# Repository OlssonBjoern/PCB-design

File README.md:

# PCB-design
Different PCB-designs to practice design in KiCad

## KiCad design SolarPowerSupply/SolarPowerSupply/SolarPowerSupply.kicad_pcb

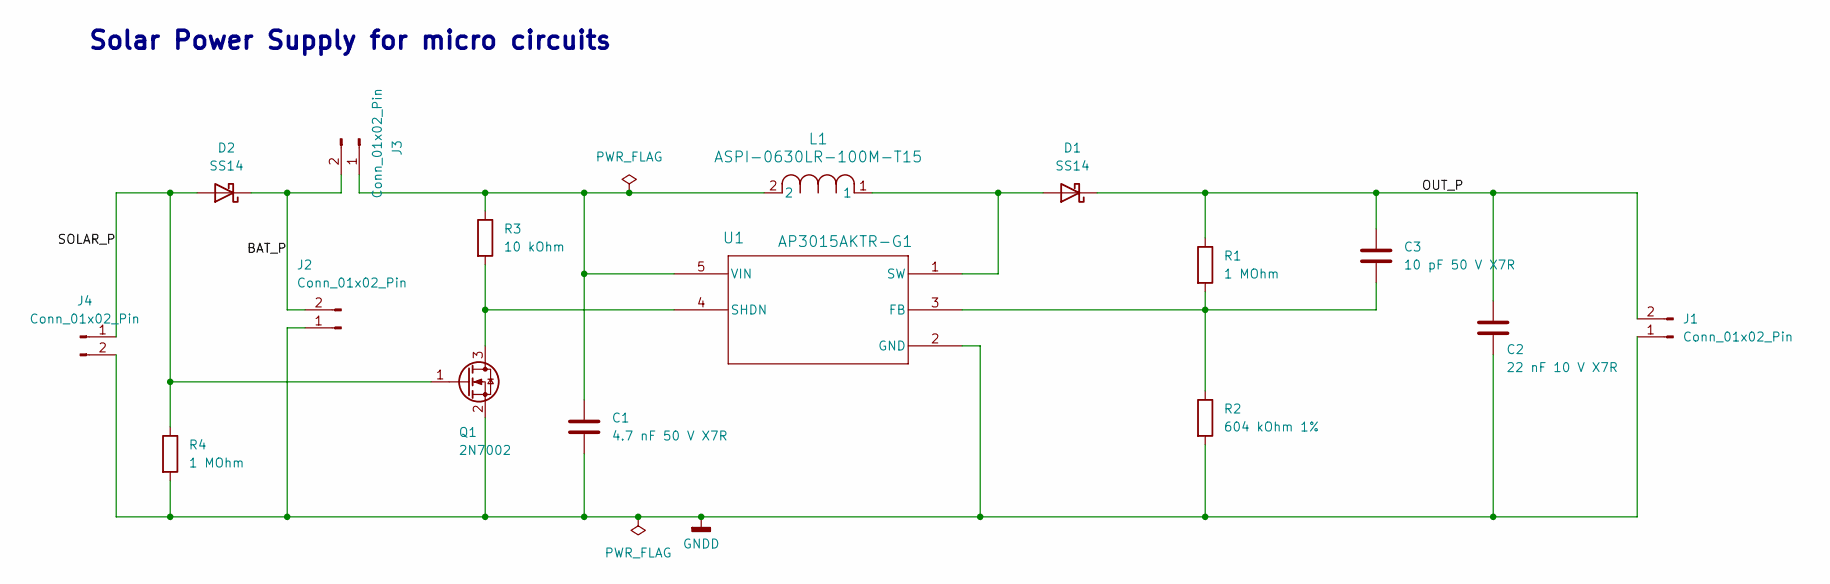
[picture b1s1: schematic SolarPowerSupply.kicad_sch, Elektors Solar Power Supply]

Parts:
C1: 4.7 nF 50 V X7R; C_0805_2012Metric
C2: 22 nF 10 V X7R; C_1206_3216Metric
C3: 10 pF 50 V X7R; C_0805_2012Metric
D1, D2: SS14; D_SMA
J1, J2: Conn_01x02_Pin; PinHeader_1x02_P2.54mm_Horizontal
J3: Conn_01x02_Pin; SW_DIP_SPSTx01_Slide_9.78x4.72mm_W7.62mm_P2.54mm
J4: Conn_01x02_Pin; PinHeader_1x02_P2.00mm_Horizontal
L1: ASPI-0630LR-100M-T15; IND_ASPI-0630LR_ABR
Q1: 2N7002; SOT-23
R1, R4: 1 MOhm; R_0805_2012Metric
R2: 604 kOhm 1%; R_0805_2012Metric
R3: 10 kOhm; R_0805_2012Metric
U1: AP3015AKTR-G1; SOT23-5_1P55X2P9_DIO

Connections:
/<NO NET>: C2.1, C3.1, D1.1 (K), J1.2, R1.1
/BAT_P: D2.1 (K), J2.2, J3.2
/SOLAR_P: D2.2 (A), J4.1, Q1.1 (G), R4.1
GNDD: C1.2, C2.2, J1.1, J2.1, J4.2, Q1.2 (S), R2.2, R4.2, U1.2 (GND)
unnamed: D1.2 (A), L1.1, U1.1 (SW)
unnamed: C1.1, J3.1, L1.2, R3.1, U1.5 (VIN)
unnamed: Q1.3 (D), R3.2, U1.4 (SHDN)
unnamed: C3.2, R1.2, R2.1, U1.3 (FB)

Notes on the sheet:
Solar Power Supply for micro circuits

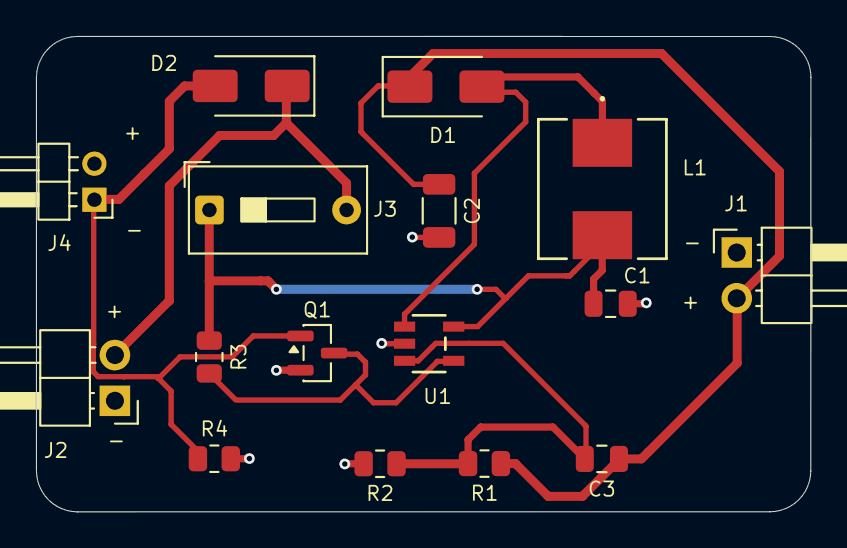
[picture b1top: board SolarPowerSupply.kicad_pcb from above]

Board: 2 copper layers, 43.0 x 26.4 mm, 16 parts (0 on the bottom side), 8 nets.

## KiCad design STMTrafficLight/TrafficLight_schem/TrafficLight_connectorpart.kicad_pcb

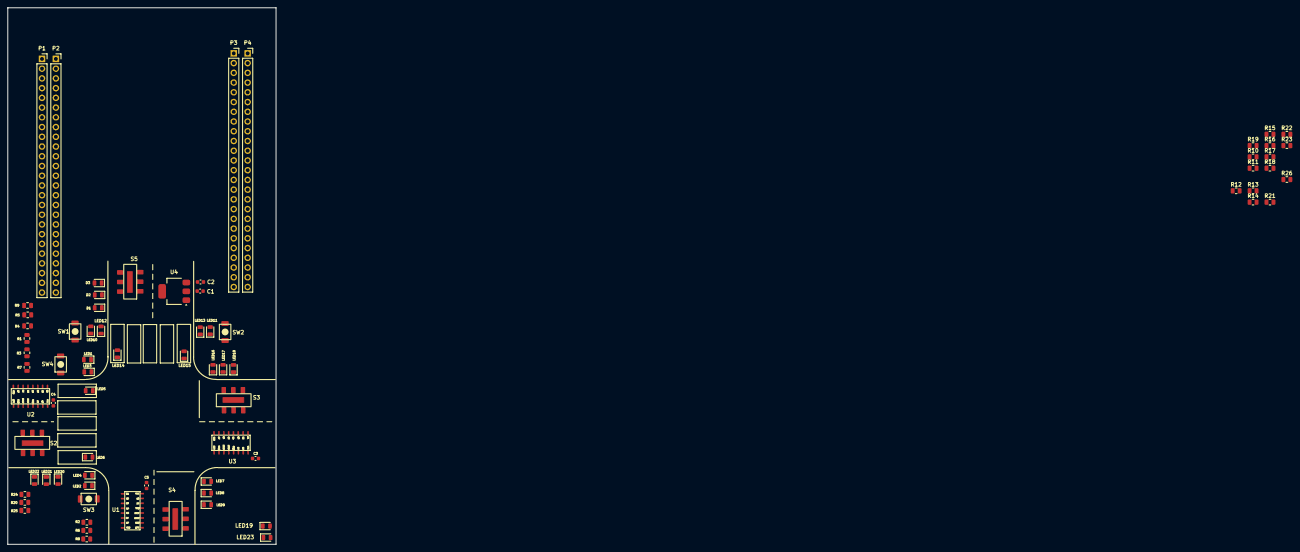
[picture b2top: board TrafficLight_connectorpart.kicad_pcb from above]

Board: 2 copper layers, 70.0 x 140.0 mm, 73 parts (0 on the bottom side), 56 nets, no tracks yet.

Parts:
C1, C2: 10uF; C_0603_1608Metric
C3, C4, C5: 100 nF; C_0603_1608Metric
D1: Red; LED_0805_2012Metric
D2: yellow; LED_0805_2012Metric
D3: green; LED_0805_2012Metric
LED1, LED2, LED7, LED10, LED11, LED16, LED20, LED23: Red; LED_0805_2012Metric
LED3, LED4, LED9, LED12, LED13, LED18, LED22: green; LED_0805_2012Metric
LED5, LED6, LED8, LED14, LED15, LED17, LED21: yellow; LED_0805_2012Metric
LED19: Green; LED_0805_2012Metric
P1, P2, P3, P4: Conn_01x25; PinSocket_1x25_P2.54mm_Vertical
R1, R2, R4, R5, R7, R8, R10, R11, R13, R14, R15, R16, R21, R22, R24, R25: 330; R_0805_2012Metric
R3, R6, R9, R12, R17, R18, R19, R20: 220; R_0805_2012Metric
R23, R26: 1k; R_0805_2012Metric
S2, S3, S4, S5: SW_slide_car; Sw_slide_car
SW1, SW2, SW3, SW4: SW_Push; sw_pedestrian_btn
U1, U2, U3: 74HC595D
U4: LM1117MP-3.3; SOT-223-3_TabPin2

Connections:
595_Enable: U1.13 (OE), U2.13 (OE), U3.13 (OE)
595_Reset: U1.10 (MR), U2.10 (MR), U3.10 (MR)
595_SHCP_SPI1_CLK: U1.11 (SHCP), U2.11 (SHCP), U3.11 (SHCP)
595_STCP_RCLK: U1.12 (STCP), U2.12 (STCP), U3.12 (STCP)
+3.3V: C3.1, C4.1, C5.1, S2.4, S3.4, S4.4, S5.4, U1.16 (VCC), U2.16 (VCC), U3.16 (VCC)
+3V3: C1.1, U4.2 (VO)
+5V: C2.1, U4.3 (VI)
GND: C1.2, C2.2, C3.2, C4.2, C5.2, D1.1 (K), D2.1 (K), D3.1 (K), LED1.1 (K), LED2.1 (K), LED3.1 (K), LED4.1 (K), LED5.1 (K), LED6.1 (K), LED7.1 (K), LED8.1 (K), LED9.1 (K), LED10.1 (K), LED11.1 (K), LED12.1 (K), LED13.1 (K), LED14.1 (K), LED15.1 (K), LED16.1 (K), LED17.1 (K), LED18.1 (K), LED19.1 (K), LED20.1 (K), LED21.1 (K), LED22.1 (K), LED23.1 (K), S2.6, S3.6, S4.6, S5.6, SW1.2, SW2.2, SW3.2, SW4.2, U1.8 (GND), U2.8 (GND), U3.8 (GND), U4.1 (GND)
unnamed: D1.2 (A), R4.2
unnamed: D2.2 (A), R5.2
unnamed: D3.2 (A), R9.2
unnamed: LED1.2 (A), R1.2
unnamed: LED2.2 (A), R2.2
unnamed: LED3.2 (A), R3.2
unnamed: LED4.2 (A), R6.2
unnamed: LED5.2 (A), R7.2
unnamed: LED6.2 (A), R8.2
unnamed: LED7.2 (A), R10.2
unnamed: LED8.2 (A), R11.2
unnamed: LED9.2 (A), R12.2
unnamed: LED10.2 (A), R13.2
unnamed: LED11.2 (A), R14.2
unnamed: LED12.2 (A), R17.2
unnamed: LED13.2 (A), R18.2
unnamed: LED14.2 (A), R15.2
unnamed: LED15.2 (A), R16.2
unnamed: LED16.2 (A), R21.2
unnamed: LED17.2 (A), R22.2
unnamed: LED18.2 (A), R19.2
unnamed: LED19.2 (A), R23.2
unnamed: LED20.2 (A), R24.2
unnamed: LED21.2 (A), R25.2
unnamed: LED22.2 (A), R20.2
unnamed: LED23.2 (A), R26.2
PL1_Green: R3.1, R6.1, U1.4 (Q4)
PL1_Red: R1.1, R2.1, U1.3 (Q3)
PL1_Switch: SW3.1, SW4.1
PL1_Yellow: R7.1, R8.1, U1.5 (Q5)
PL2_Green: R17.1, R18.1, U2.4 (Q4)
PL2_Red: R13.1, R14.1, U2.3 (Q3)
PL2_Switch: SW1.1, SW2.1
PL2_Yellow: R15.1, R16.1, U2.5 (Q5)
TL1_Green: R9.1, U1.2 (Q2)
TL1_Red: R4.1, U1.15 (Q0)
TL1_Yellow: R5.1, U1.1 (Q1)
TL2_Green: R20.1, U2.2 (Q2)
TL2_Red: R24.1, U2.15 (Q0)
TL2_Yellow: R25.1, U2.1 (Q1)
TL3_Green: R19.1, U3.2 (Q2)
TL3_Red: R21.1, U3.15 (Q0)
TL3_Yellow: R22.1, U3.1 (Q1)
TL4_Green: R12.1, U3.5 (Q5)
TL4_Red: R10.1, U3.3 (Q3)
TL4_Yellow: R11.1, U3.4 (Q4)
U1_DO: U1.9 (Q7S), U2.14 (DS)
U2_DO: U2.9 (Q7S), U3.14 (DS)

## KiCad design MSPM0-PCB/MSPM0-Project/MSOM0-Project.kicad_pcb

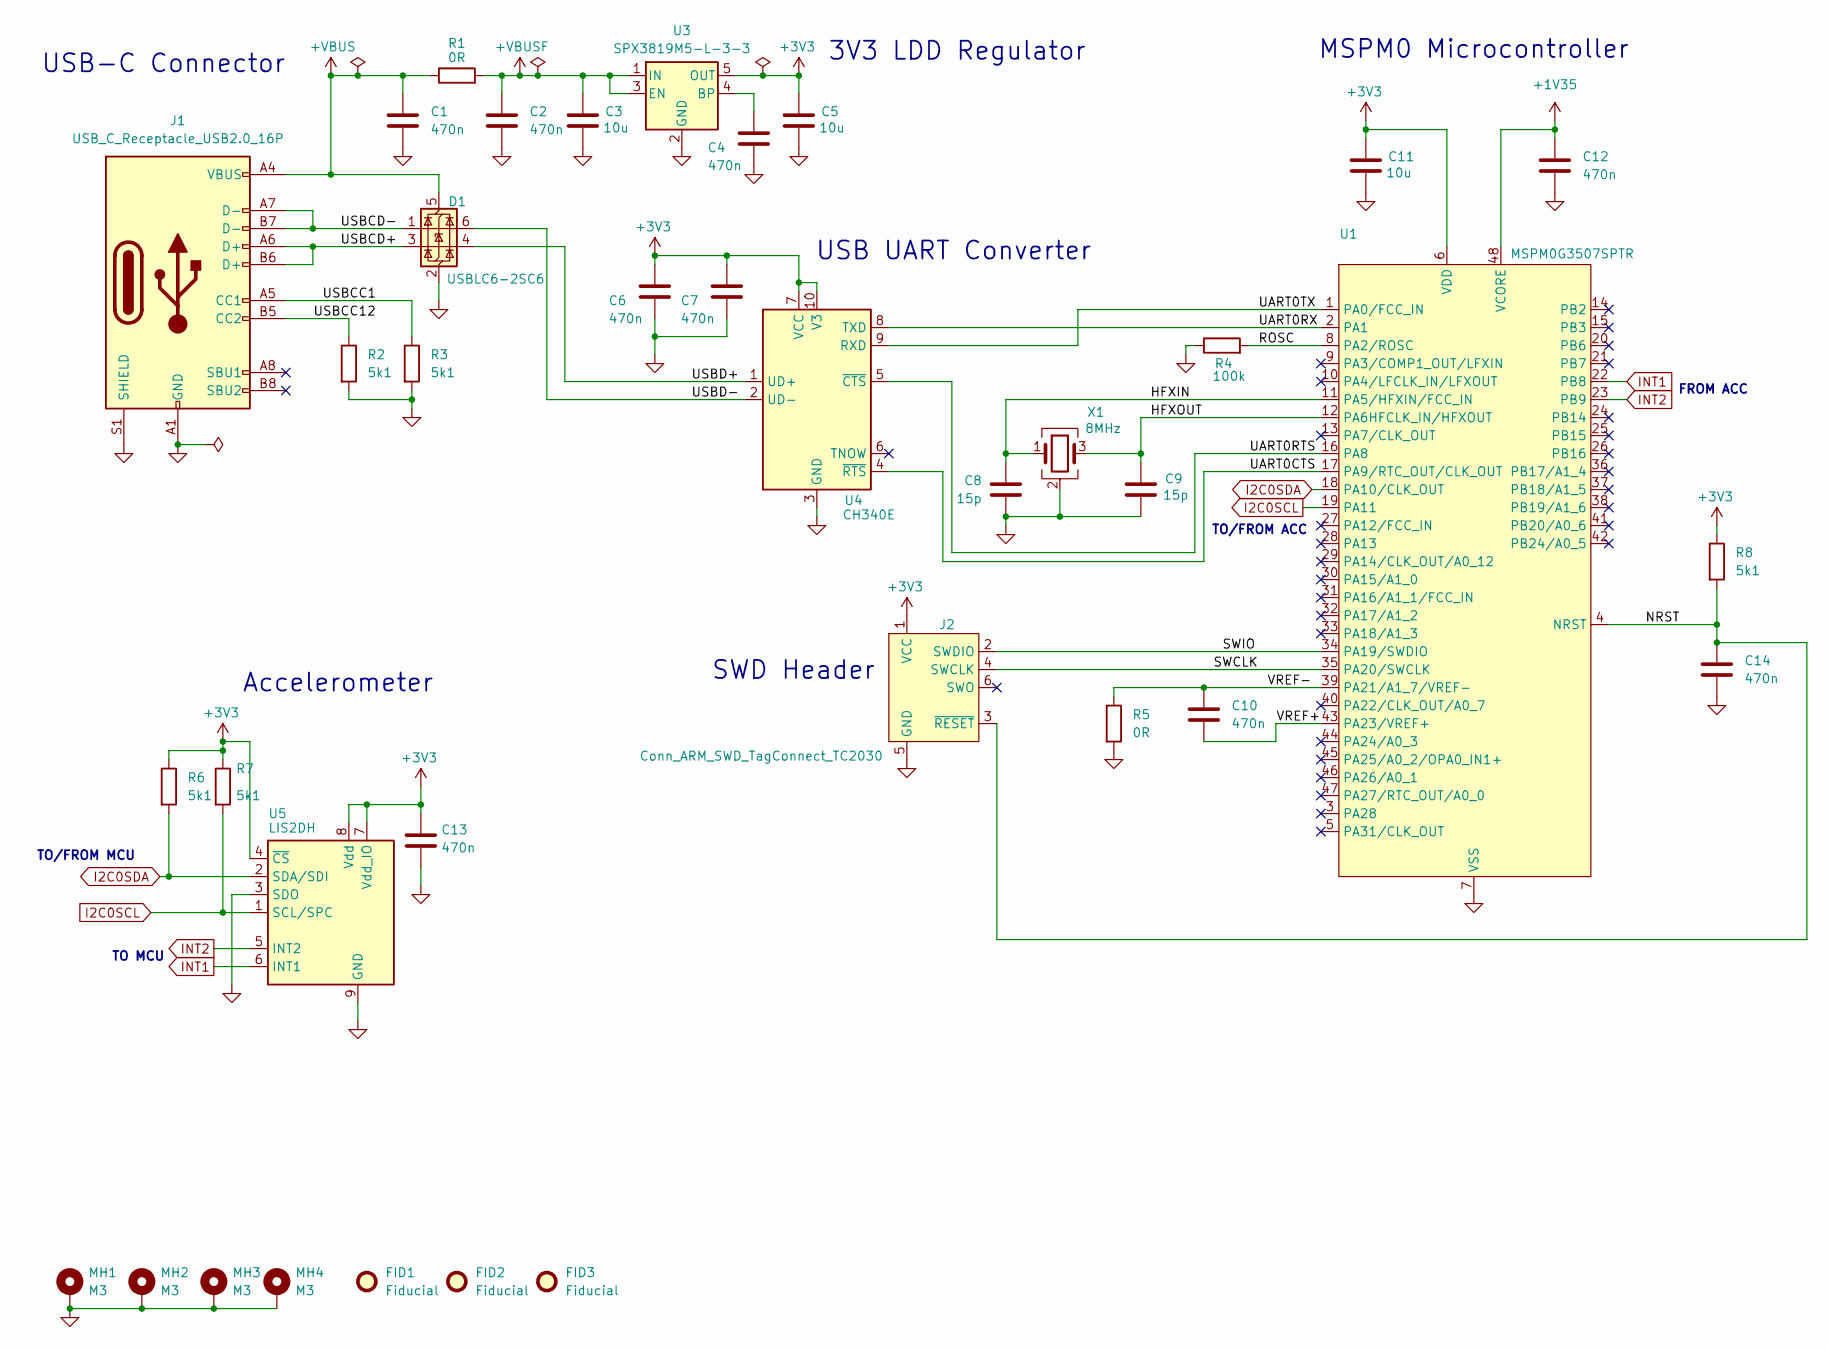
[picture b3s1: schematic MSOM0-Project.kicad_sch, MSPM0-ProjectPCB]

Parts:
C1, C2, C4, C6, C7, C10, C12, C13, C14: 470n; C_0603_1608Metric; Manufacturer part number CL21B474KBFNNNE; LCSC C13967
C3, C5, C11: 10u; C_0805_2012Metric; Manufacturer part number CL21A106KAYQNWE; LCSC C3887226
C8, C9: 15p; C_0603_1608Metric; Manufacturer part number CL21B474KBFNNNE; LCSC C13967
D1: USBLC6-2SC6; SOT-23-6
FID1, FID2, FID3: Fiducial; Fiducial_1mm_Mask2mm
J1: USB_C_Receptacle_USB2.0_16P; USB_C_Receptacle_GCT_USB4105-xx-A_16P_TopMnt_Horizontal; Manufacturer part number USB4105-GF-A-120; LCSC C5184243
J2: Conn_ARM_SWD_TagConnect_TC2030; Tag-Connect_TC2030-IDC-FP_2x03_P1.27mm_Vertical
MH1, MH2, MH3, MH4: M3; MountingHole_3.2mm_M3_Pad_Via
R1, R5: 0R; R_0603_1608Metric; Manufacturer part number 0603WAF0000T5E; LCSC C21189
R2, R3, R6, R7, R8: 5k1; R_0603_1608Metric; Manufacturer part number 0603WAF5101T5E; LCSC C23186
R4: 100k; R_0603_1608Metric; Manufacturer part number RT73F1J100KBTD
U1: MSPM0G3507SPTR; LQFP-48_7x7mm_P0.5mm; Manufacturer Part Number MSPM0G3507SPTR; LCSC C22362630
U3: SPX3819M5-L-3-3; SOT-23-5
U4: CH340E; MSOP-10_3x3mm_P0.5mm; Manufacturer part number CH340E; LCSC C99652
U5: LIS2DH; LGA-14_2x2mm_P0.35mm_LayoutBorder3x4y; Manufacturer part number LIS2DH12TR; LCSC C110926
X1: 8MHz; Crystal_SMD_3225-4Pin_3.2x2.5mm; Manufacturer Part number ECS-80-12-33-JGN-TR; LCSC C2442665

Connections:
+1V35: C12.1, U1.48 (VCORE)
+3V3: C5.1, C6.1, C7.1, C11.1, C13.1, J2.1 (VCC), R6.1, R7.1, R8.1, U1.6 (VDD), U3.5 (OUT), U4.7 (VCC), U4.10 (V3), U5.4 (~CS), U5.7 (Vdd_IO), U5.8 (Vdd)
+VBUS: C1.1, D1.5 (VBUS), J1.A4 (VBUS), J1.A9 (VBUS), J1.B4 (VBUS), J1.B9 (VBUS), R1.1
+VBUSF: C2.1, C3.1, R1.2, U3.1 (IN), U3.3 (EN)
/HFXIN: C8.1, U1.11 (PA5/HFXIN/FCC_IN), X1.1
/HFXOUT: C9.1, U1.12 (PA6HFCLK_IN/HFXOUT), X1.3
/NRST: C14.1, J2.3 (~RESET), R8.2, U1.4 (NRST)
/ROSC: R4.2, U1.8 (PA2/ROSC)
/SWCLK: J2.4 (SWCLK), U1.35 (PA20/SWCLK)
/SWIO: J2.2 (SWDIO), U1.34 (PA19/SWDIO)
/UART0CTS: U1.17 (PA9/RTC_OUT/CLK_OUT), U4.4 (~RTS)
/UART0RTS: U1.16 (PA8), U4.5 (~CTS)
/UART0RX: U1.2 (PA1), U4.8 (TXD)
/UART0TX: U1.1 (PA0/FCC_IN), U4.9 (RXD)
/USBCC1: J1.A5 (CC1), R3.1
/USBCC12: J1.B5 (CC2), R2.1
/USBCD+: D1.3 (I/O2), J1.A6 (D+), J1.B6 (D+)
/USBCD-: D1.1 (I/O1), J1.A7 (D-), J1.B7 (D-)
/USBD+: D1.4 (I/O2), U4.1 (UD+)
/USBD-: D1.6 (I/O1), U4.2 (UD-)
/VREF+: C10.2, U1.43 (PA23/VREF+)
/VREF-: C10.1, R5.1, U1.39 (PA21/A1_7/VREF-)
I2C0SCL: R7.2, U1.19 (PA11), U5.1 (SCL/SPC)
I2C0SDA: R6.2, U1.18 (PA10/CLK_OUT), U5.2 (SDA/SDI)
INT1: U1.22 (PB8), U5.6 (INT1)
INT2: U1.23 (PB9), U5.5 (INT2)
unnamed: C4.1, U3.4 (BP)

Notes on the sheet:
TO/FROM MCU
USB UART Converter
USB-C Connector
MSPM0 Microcontroller
Accelerometer
TO MCU
TO/FROM ACC
3V3 LDD Regulator
SWD Header
FROM ACC

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
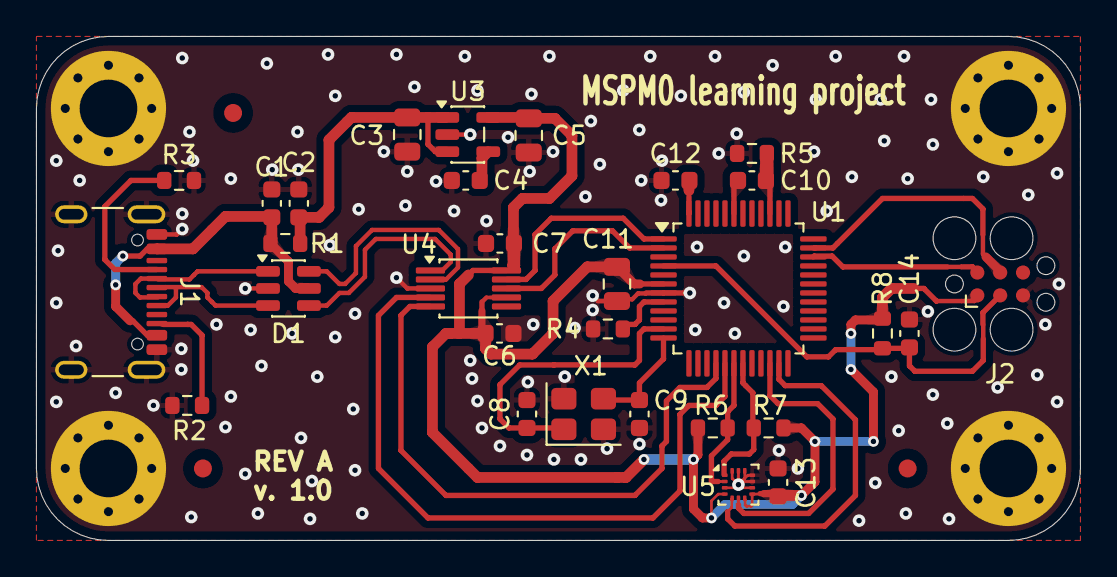
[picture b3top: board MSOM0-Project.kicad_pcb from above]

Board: 2 copper layers, 58.0 x 28.0 mm, 37 parts (0 on the bottom side), 28 nets.

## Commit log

2026-03-17 clean repo (removed large files)
2026-03-24 added pcb layout
2026-03-25 removed key
2026-03-25 making test
2026-03-29 started on the traffic light shield
2026-03-30 continued on the traffic light shield
2026-04-07 Marked connectors and added power LEDs, fixed resistors
2026-04-10 Finally started the PCB design
2026-04-16 Added silk screen and edge cutouts
2026-05-07 Added routes and new compontents to solar power
2026-05-10 Finished solar power
2026-05-13 Started LED matrix schematic
